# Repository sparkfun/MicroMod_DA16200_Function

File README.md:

SparkFun MicroMod DA16200 Function Board
========================================

[*SparkFun MicroMod DA16200 Function Board (18594)*](https://www.sparkfun.com/products/18594)

The SparkFun MicroMod DA16200 Function Board adds a fully integrated WiFi module with a 40MHz crystal oscillator, 32.768KHz RTC clock, RF Lumped RF filter, 4MB flash memory, and an on-board chip antenna to any MicroMod project. With the addition of JTAG connectors for deep dive programming, you've got everything you need to get your MicroMod setup ready for your next IoT project. 

The SparkFun MicroMod DA16200 Function Board is ideal for MicroMod projects involving door locks, thermostats, sensors, pet trackers, and other home IoT projects, thanks in part to the multiple sleep modes that allow you to take advantage of current draws as low as 0.2uA-3.5uA.

Additionally, the DA16200 module's certified WiFi alliance for IEEE802.11b/g/n, WiFi Direct, and WPS functionalities means that it has been approved for use by multiple countries and using the WiFi Alliance transfer policy, each WiFi Certification can be transferred without being tested again. 

Repository Contents
-------------------
* **/Hardware** - Eagle design files (.brd, .sch)

Documentation
--------------
* **[Hookup Guide](https://learn.sparkfun.com/tutorials/micromod-wifi-function-board---da16200-hookup-guide)** - Basic hookup guide for the SparkFun MicroMod DA16200 Function Board.

License Information
-------------------

This product is _**open source**_! 

Please review the LICENSE.md file for license information. 

If you have any questions or concerns on licensing, please contact technical support on our [SparkFun forums](https://forum.sparkfun.com/viewforum.php?f=152).

Distributed as-is; no warranty is given.

- Your friends at SparkFun.

_<COLLABORATION CREDIT>_

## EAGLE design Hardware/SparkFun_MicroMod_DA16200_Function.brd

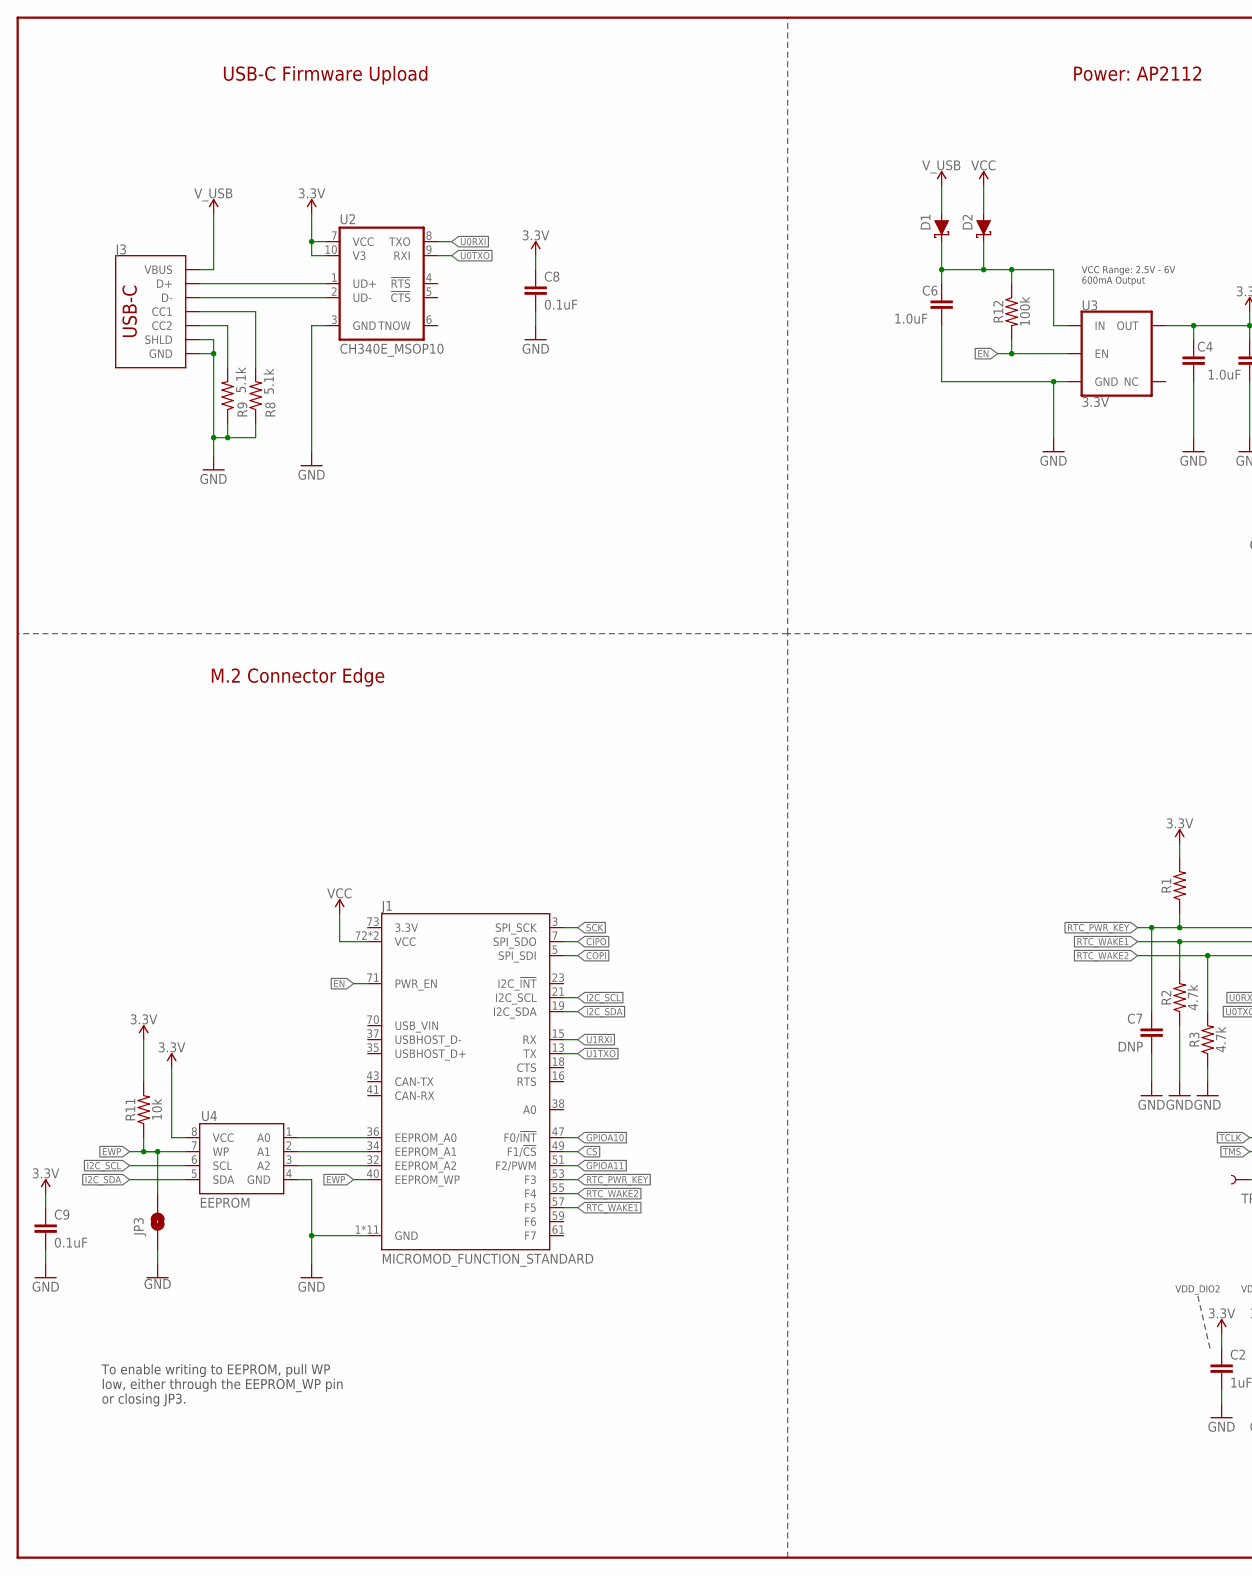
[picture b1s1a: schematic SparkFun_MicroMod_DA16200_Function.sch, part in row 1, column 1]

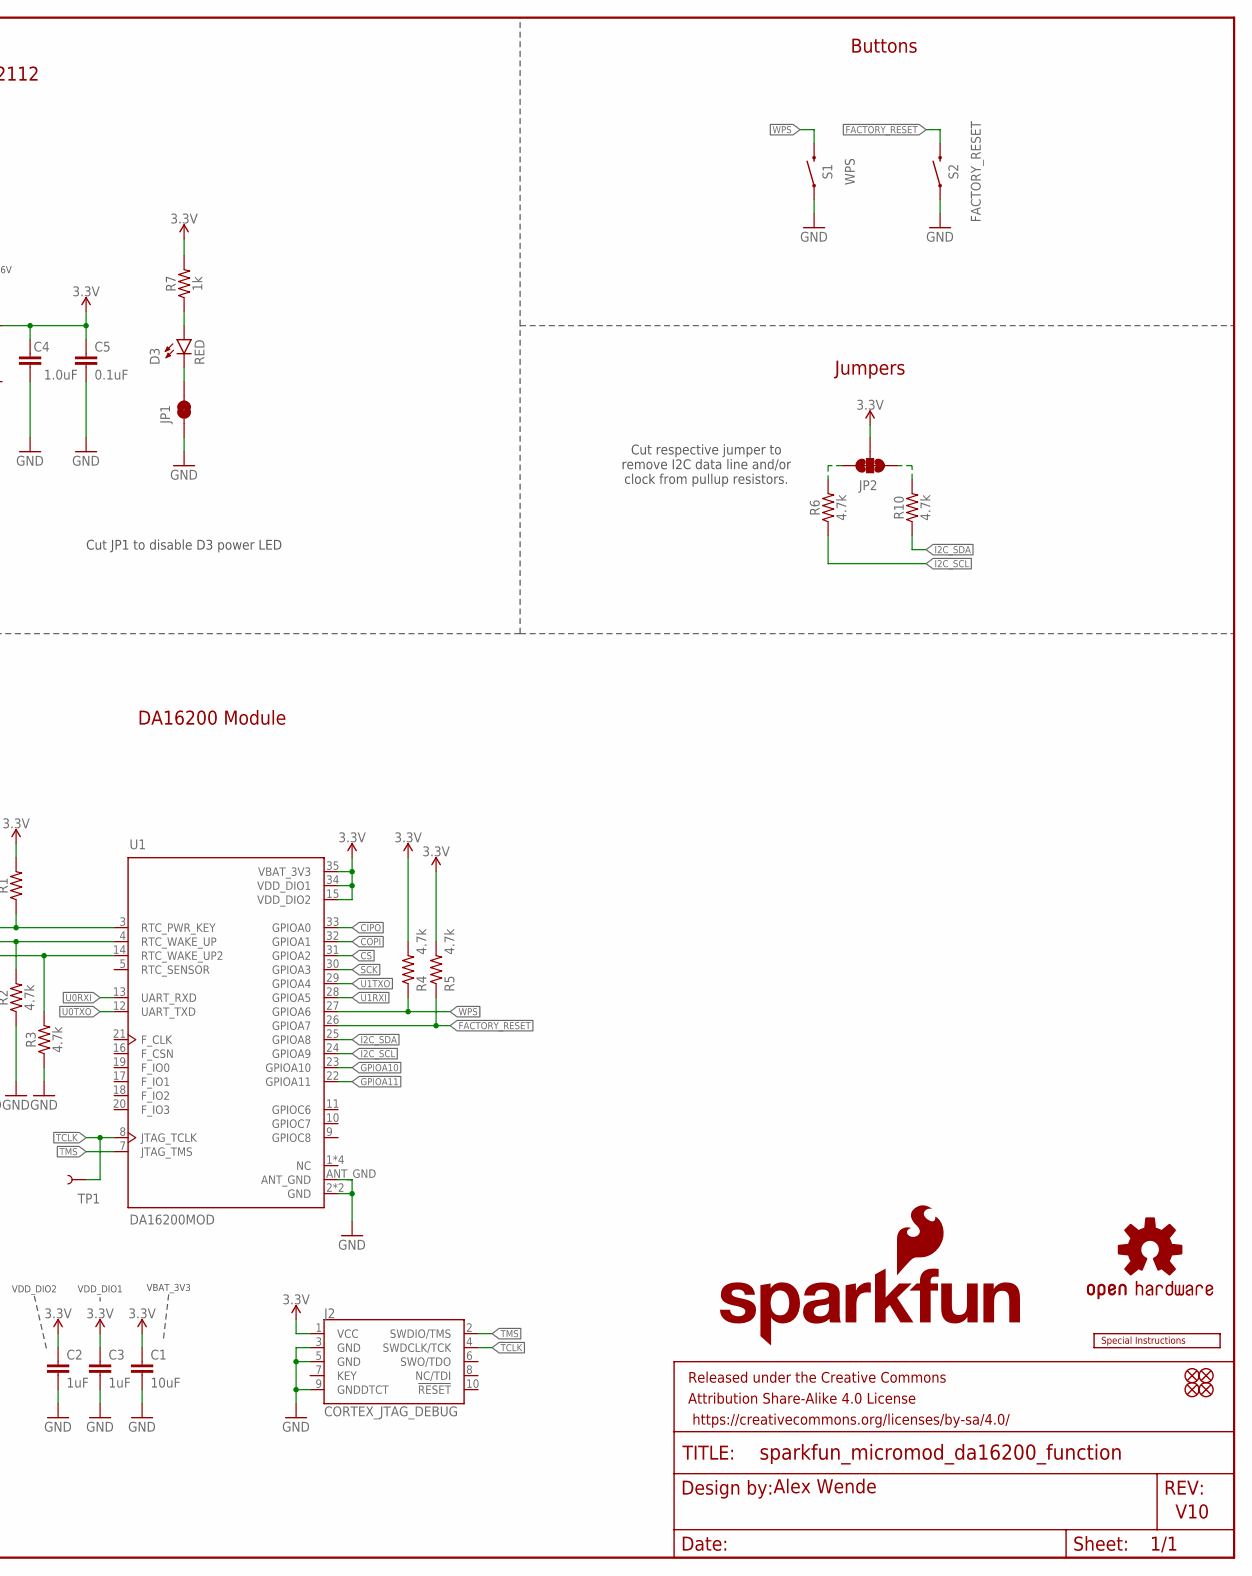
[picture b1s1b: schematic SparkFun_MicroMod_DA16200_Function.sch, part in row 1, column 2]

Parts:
C1: 10uF; 0603
C2, C3: 1uF; 0603
C4, C6: 1.0uF; 0603
C5, C8, C9: 0.1uF; 0603
C7: DNP; 0603
D1, D2: DIODE-SCHOTTKY-BAT60A; SOD-323
D3: RED; LED-0603
FD1, FD2, FD3, FD4: FIDUCIAL1X2; FIDUCIAL-1X2
FRAME2: FRAME-LEDGER; CREATIVE_COMMONS
J1: MICROMOD_FUNCTION_STANDARD; M.2-CARD-E-22_FUNCTION_STANDARD
J2: CORTEX_JTAG_DEBUG; 2X5-PTH-1.27MM-NO_SILK
J3: USB_C_2-LAYER_PADS; USB-C-16P-2LAYER-PADS
JP1: JUMPER-SMT_2_NC_TRACE_SILK; SMT-JUMPER_2_NC_TRACE_SILK
JP2: JUMPER-SMT_3_2-NC_TRACE_SILK; SMT-JUMPER_3_2-NC_TRACE_SILK
JP3: JUMPER-SMT_2_NO_SILK; SMT-JUMPER_2_NO_SILK
LOGO1: SFE_LOGO_NAME_FLAME.2_INCH; SFE_LOGO_NAME_FLAME_.2
LOGO2: OSHW-LOGOS; OSHW-LOGO-S
LOGO3: SPECIAL_INSTRUCTIONS-ORDERING; ORDERING_INSTRUCTIONS
R1: 0603
R2, R3, R4, R5, R6, R10: 4.7k; 0603
R7: 1k; 0402-TIGHT
R8, R9: 5.1k; 0402-TIGHT
R11: 10k; 0603
R12: 100k; 0603
S1: WPS; TACTILE_SWITCH_SMD_5.2MM
S2: FACTORY_RESET; TACTILE_SWITCH_SMD_5.2MM
TP1: TEST-POINT3; PAD.03X.03
U1: DA16200MOD; XCVR_DA16200MOD-AAC4WA32
U2: CH340E_MSOP10; MSOP10
U3: 3.3V; SOT23-5
U4: EEPROM; SO08

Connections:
3.3V: C1.1, C2.1, C3.1, C4.1, C5.1, C8.1, C9.1, J2.1 (VCC), JP2.2, R1.2, R4.2, R5.2, R7.2, R11.2, U1.15 (VDD_DIO2), U1.34 (VDD_DIO1), U1.35 (VBAT_3V3), U2.7 (VCC), U2.10 (V3), U3.5 (OUT), U4.8 (VCC)
!CS!: J1.49 (F1/!CS!), U1.31 (GPIOA2)
CIPO: J1.7 (SPI_SDO), U1.33 (GPIOA0)
COPI: J1.5 (SPI_SDI), U1.32 (GPIOA1)
EN: J1.71 (PWR_EN), R12.2, U3.3 (EN)
EWP: J1.40 (EEPROM_WP), JP3.2, R11.1, U4.7 (WP)
FACTORY_RESET: R5.1, S2.3 (2), U1.26 (GPIOA7)
GND: C1.2, C2.2, C3.2, C4.2, C5.2, C6.2, C7.2, C8.2, C9.2, J1.1 (GND), J1.33 (GND), J1.39 (GND), J1.45 (GND), J1.75 (GND), J1.GND1 (GND), J1.GND2 (GND), J1.GND3 (GND), J1.GND4 (GND), J1.GND5 (GND), J1.GND6 (GND), J2.3 (GND), J2.5 (GND), J2.9 (GNDDTCT), J3.GND, J3.GND2 (GND), J3.SHLD1 (SHLD), J3.SHLD2 (SHLD), J3.SHLD3 (SHLD), J3.SHLD4 (SHLD), JP1.1, JP3.1, R2.1, R3.1, R8.1, R9.1, S1.1, S2.1, U1.2 (GND), U1.ANT_GND, U1.GND, U2.3 (GND), U3.2 (GND), U4.4 (GND)
GPIOA10: J1.47 (F0/!INT!), U1.23 (GPIOA10)
GPIOA11: J1.51 (F2/PWM), U1.22 (GPIOA11)
I2C_SCL: J1.21 (I2C_SCL), R6.1, U1.24 (GPIOA9), U4.6 (SCL)
I2C_SDA: J1.19 (I2C_SDA), R10.1, U1.25 (GPIOA8), U4.5 (SDA)
unnamed: J1.36 (EEPROM_A0), U4.1 (A0)
unnamed: J3.A5 (CC1), R8.2
unnamed: C6.1, D1.C, D2.C, R12.1, U3.1 (IN)
unnamed: J3.B5 (CC2), R9.2
unnamed: D3.C, JP1.2
unnamed: D3.A, R7.1
unnamed: J1.32 (EEPROM_A2), U4.3 (A2)
unnamed: J1.34 (EEPROM_A1), U4.2 (A1)
unnamed: J3.A6 (D+), J3.B6 (D+), U2.1 (UD+)
unnamed: J3.A7 (D-), J3.B7 (D-), U2.2 (UD-)
unnamed: JP2.1, R10.2
unnamed: JP2.3, R6.2
RTC_PWR_KEY: C7.1, J1.53 (F3), R1.1, U1.3 (RTC_PWR_KEY)
RTC_WAKE1: J1.57 (F5), R2.2, U1.4 (RTC_WAKE_UP)
RTC_WAKE2: J1.55 (F4), R3.2, U1.14 (RTC_WAKE_UP2)
SCK: J1.3 (SPI_SCK), U1.30 (GPIOA3)
TCLK: J2.4 (SWDCLK/TCK), TP1.1, U1.8 (JTAG_TCLK)
TMS: J2.2 (SWDIO/TMS), U1.7 (JTAG_TMS)
U0RXI: U1.13 (UART_RXD), U2.8 (TXO)
U0TXO: U1.12 (UART_TXD), U2.9 (RXI)
U1RXI: J1.15 (RX), U1.28 (GPIOA5)
U1TXO: J1.13 (TX), U1.29 (GPIOA4)
VCC: D2.A, J1.72 (VCC), J1.74 (VCC)
V_USB: D1.A, J3.VBUS1 (VBUS), J3.VBUS2 (VBUS)
WPS: R4.1, S1.3 (2), U1.27 (GPIOA6)

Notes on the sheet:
VCC Range: 2.5V - 6V 600mA Output
VDD_DIO2
VDD_DIO1
VBAT_3V3
Alex Wende
V10
USB-C Firmware Upload
DA16200 Module
M.2 Connector Edge
Power: AP2112
Buttons
Jumpers
Cut respective jumper to remove I2C data line and/or clock from pullup resistors.
To enable writing to EEPROM, pull WP low, either through the EEPROM_WP pin or closing JP3.
Cut JP1 to disable D3 power LED

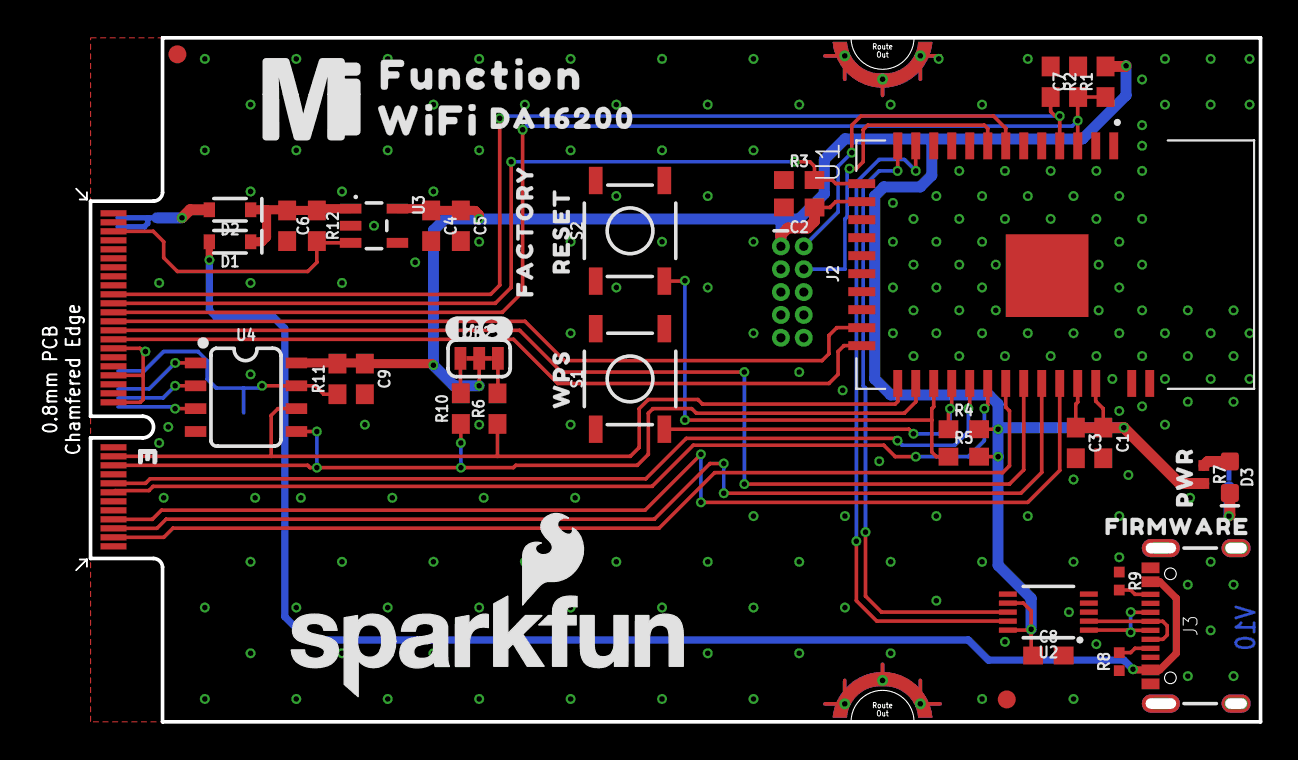
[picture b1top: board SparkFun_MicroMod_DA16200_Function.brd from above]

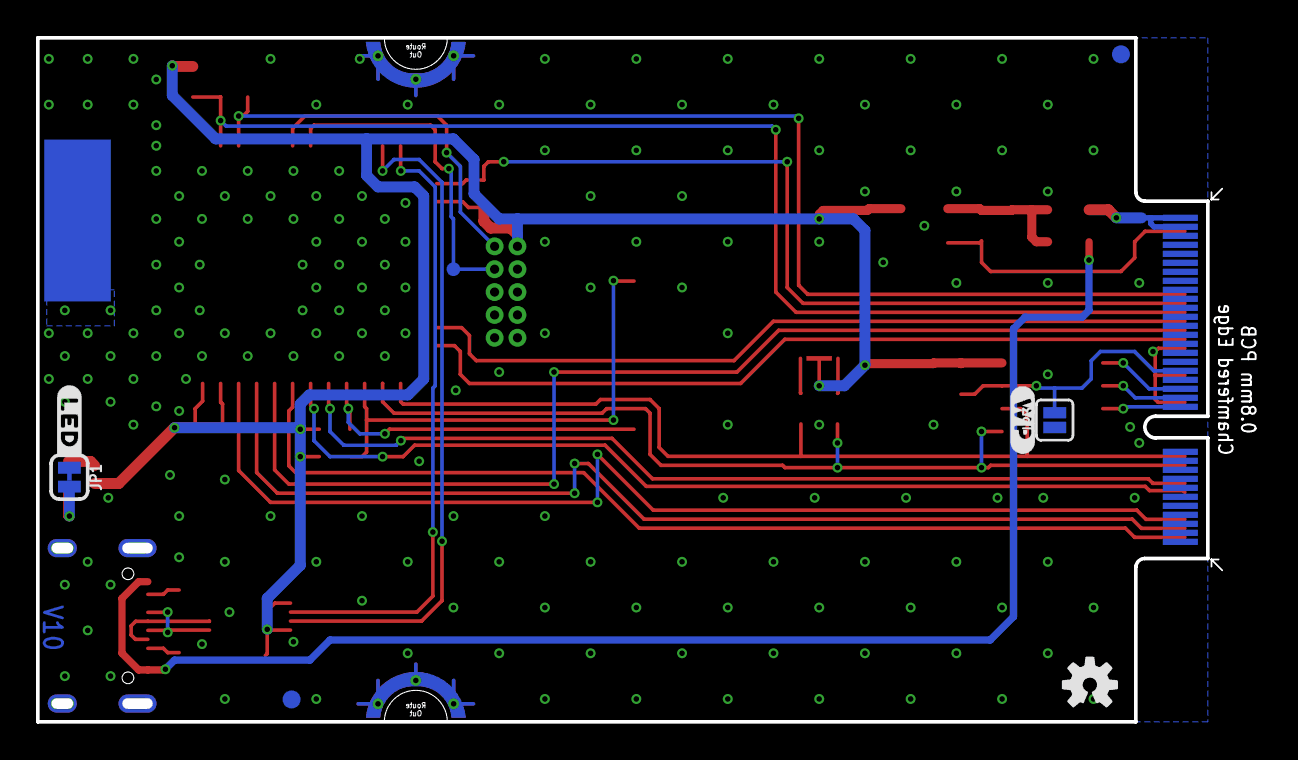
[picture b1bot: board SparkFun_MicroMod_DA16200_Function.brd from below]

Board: 2 copper layers, 65.8 x 38.0 mm, 57 parts (8 on the bottom side), 37 nets.

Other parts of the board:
U$1: FIRMWARE0
U$2: PWR0
U$3: #LED#0
U$4: FUNCTION0
U$5: DA162000
U$6: WIFI0
U$7: WPS0
U$8: FACTORY0
U$9: RESET0
U$10: #WP#0
U$11: #I2C#0
U$12: MICROMOD_MI_LOGO_1

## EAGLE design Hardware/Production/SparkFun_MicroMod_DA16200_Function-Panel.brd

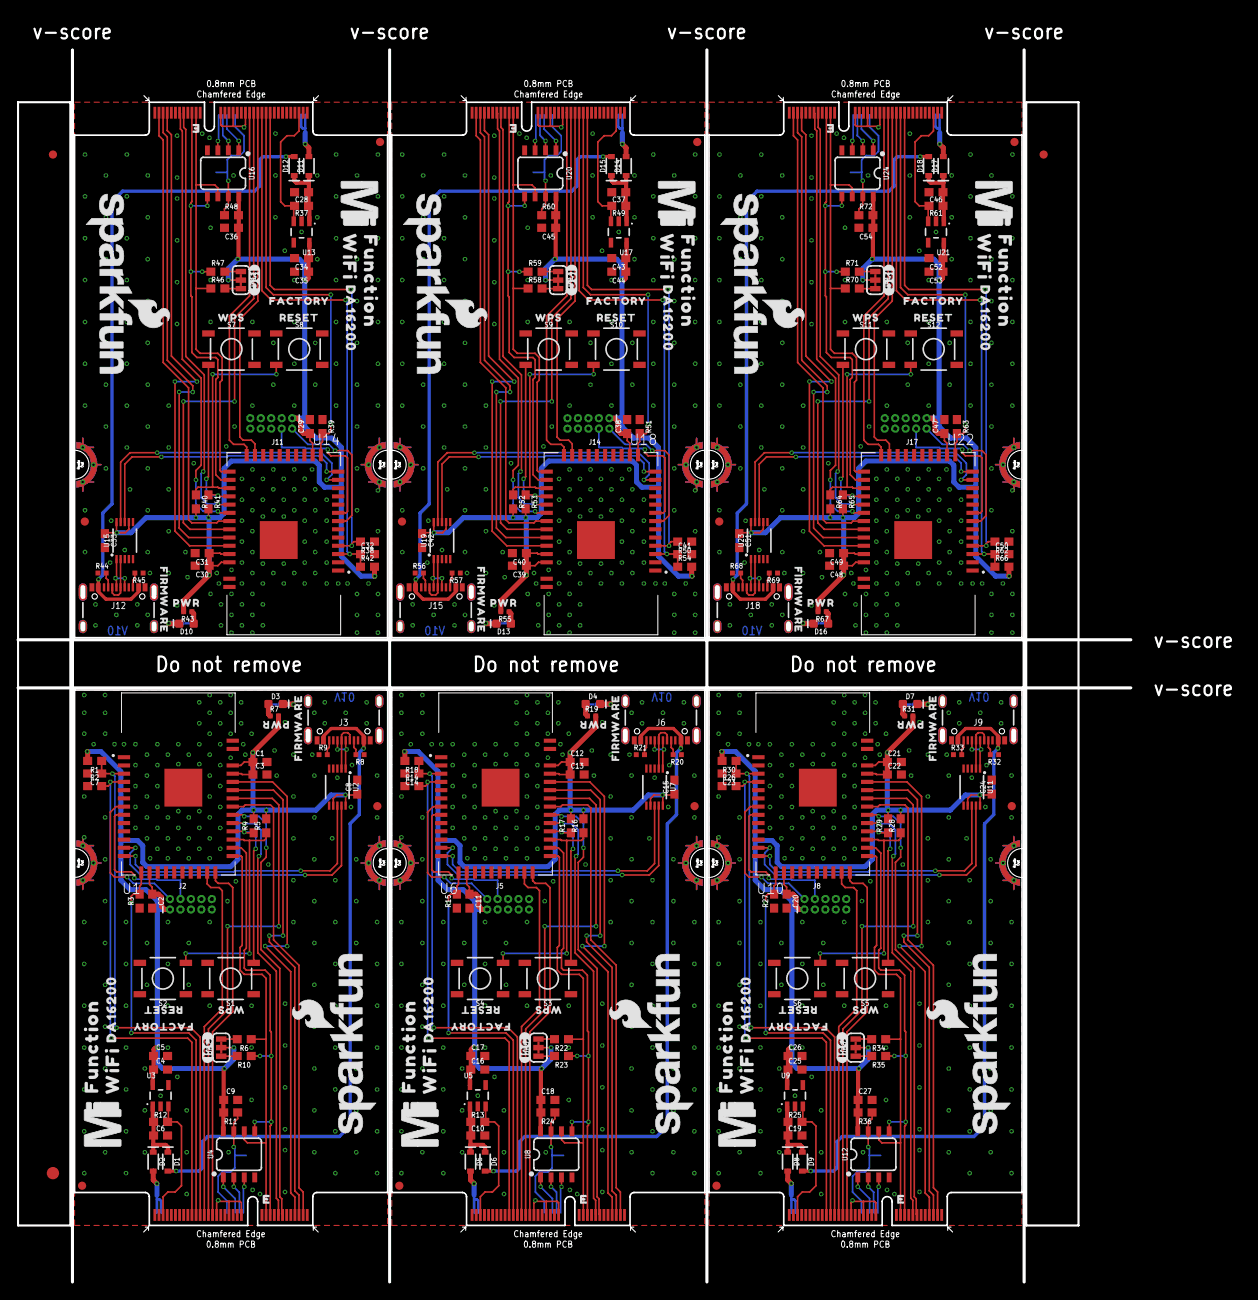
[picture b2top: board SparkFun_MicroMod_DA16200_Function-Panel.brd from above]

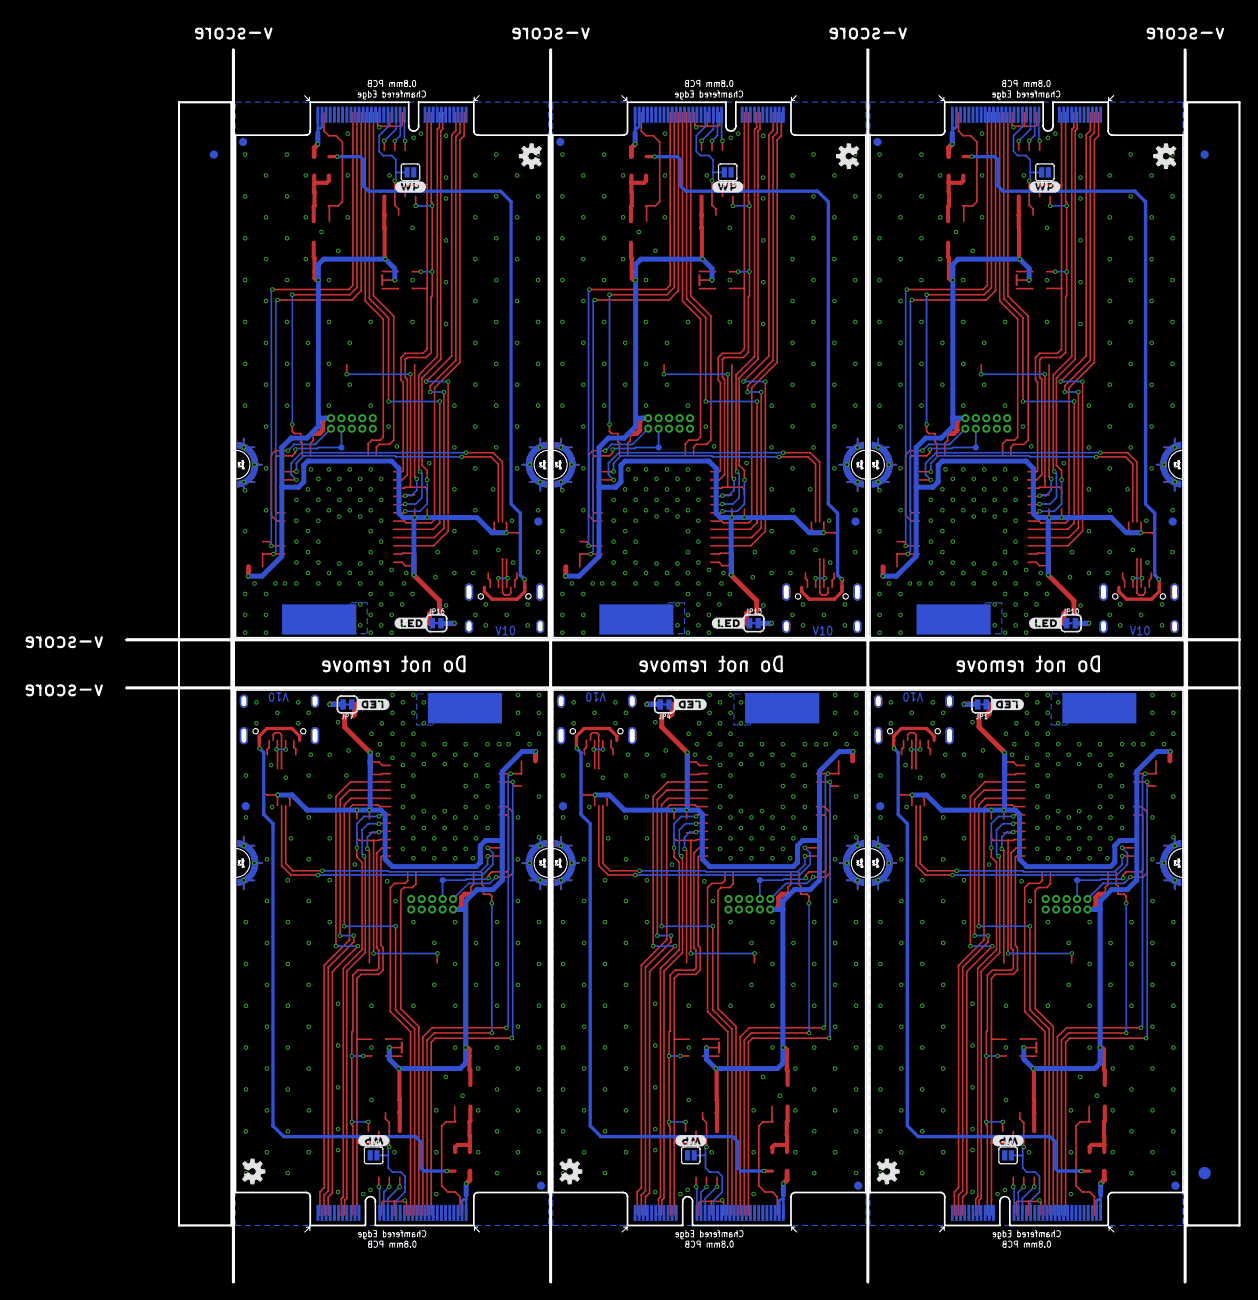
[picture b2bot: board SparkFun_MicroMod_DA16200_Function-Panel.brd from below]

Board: 2 copper layers, 135.1 x 149.6 mm, 336 parts (51 on the bottom side), 222 nets.

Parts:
C1, C12, C21, C30, C39, C48: 10uF; 0603
C2, C3, C11, C13, C20, C22, C29, C31, C38, C40, C47, C49: 1uF; 0603
C4, C6, C10, C16, C19, C25, C28, C34, C37, C43, C46, C52: 1.0uF; 0603
C5, C8, C9, C15, C17, C18, C24, C26, C27, C33, C35, C36, C42, C44, C45, C51, C53, C54: 0.1uF; 0603
C7, C14, C23, C32, C41, C50: DNP; 0603
D1, D2, D5, D6, D8, D9, D11, D12, D14, D15, D17, D18: SOD-323
D3, D4, D7, D10, D13, D16: RED; LED-0603
E$1, E$2, E$3, E$4: FIDUCIAL-1X2
E$5, E$6: FIDUCIAL-1.5X3
FD1, FD2, FD3, FD4, FD5, FD6, FD7, FD8, FD9, FD10, FD11, FD12, FD13, FD14, FD15, FD16, FD17, FD18, FD19, FD20, FD21, FD22, FD23, FD24: FIDUCIAL1X2; FIDUCIAL-1X2
J1, J4, J7, J10, J13, J16: MICROMOD_STANDARD; M.2-CARD-E-22_FUNCTION_STANDARD
J2, J5, J8, J11, J14, J17: CORTEX_JTAG_DEBUG; 2X5-PTH-1.27MM-NO_SILK
J3, J6, J9, J12, J15, J18: USB-C-16P-2LAYER-PADS
JP1, JP4, JP7, JP10, JP13, JP16: JUMPER-SMT_2_NC_TRACE_SILK; SMT-JUMPER_2_NC_TRACE_SILK
JP2, JP5, JP8, JP11, JP14, JP17: JUMPER-SMT_3_2-NC_TRACE_SILK; SMT-JUMPER_3_2-NC_TRACE_SILK
JP3, JP6, JP9, JP12, JP15, JP18: SMT-JUMPER_2_NO_SILK
LOGO1, LOGO3, LOGO5, LOGO7, LOGO9, LOGO11: SFE_LOGO_NAME_FLAME.2_INCH; SFE_LOGO_NAME_FLAME_.2
LOGO2, LOGO4, LOGO6, LOGO8, LOGO10, LOGO12: OSHW-LOGOS; OSHW-LOGO-S
R1, R18, R30, R42, R54, R66: DNP; 0603
R2, R3, R4, R5, R6, R10, R14, R15, R16, R17, R22, R23, R26, R27, R28, R29, R34, R35, R38, R39, R40, R41, R46, R47, R50, R51, R52, R53, R58, R59, R62, R63, R64, R65, R70, R71: 4.7k; 0603
R7, R19, R31, R43, R55, R67: 1k; 0402-TIGHT
R8, R9, R20, R21, R32, R33, R44, R45, R56, R57, R68, R69: 5.1k; 0402-TIGHT
R11, R24, R36, R48, R60, R72: 10k; 0603
R12, R13, R25, R37, R49, R61: 100k; 0603
S1, S3, S5, S7, S9, S11: WPS; TACTILE_SWITCH_SMD_5.2MM
S2, S4, S6, S8, S10, S12: FACTORY_RESET; TACTILE_SWITCH_SMD_5.2MM
TP1, TP2, TP3, TP4, TP5, TP6: PAD.03X.03
U1, U6, U10, U14, U18, U22: DA16200MOD; XCVR_DA16200MOD-AAC4WA32
U2, U7, U11, U15, U19, U23: CH340E_MSOP10; MSOP10
U3, U5, U9, U13, U17, U21: 3.3V; SOT23-5
U4, U8, U12, U16, U20, U24: EEPROM; SO08
U$1, U$13, U$25, U$37, U$49, U$61: FIRMWARE0
U$2, U$14, U$26, U$38, U$50, U$62: PWR0
U$3, U$15, U$27, U$39, U$51, U$63: #LED#0
U$4, U$16, U$28, U$40, U$52, U$64: FUNCTION0
U$5, U$17, U$29, U$41, U$53, U$65: DA162000
U$6, U$23, U$35, U$47, U$59, U$71: WIFI0
U$7, U$18, U$30, U$42, U$54, U$66: WPS0
U$8, U$19, U$31, U$43, U$55, U$67: FACTORY0
U$9, U$20, U$32, U$44, U$56, U$68: RESET0
U$10, U$24, U$36, U$48, U$60, U$72: #WP#0
U$11, U$21, U$33, U$45, U$57, U$69: #I2C#0
U$12, U$22, U$34, U$46, U$58, U$70: MICROMOD_MI_LOGO_1

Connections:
3.3V: C1.1, C2.1, C3.1, C4.1, C5.1, C8.1, C9.1, J2.1, JP2.2, R1.2, R4.2, R5.2, R7.2, R11.2, U1.15, U1.34, U1.35, U2.7, U2.10, U3.5, U4.8
3.3V1: C11.1, C12.1, C13.1, C15.1, C16.1, C17.1, C18.1, J5.1, JP5.2, R16.2, R17.2, R18.2, R19.2, R24.2, U5.5, U6.15, U6.34, U6.35, U7.7, U7.10, U8.8
3.3V2: C20.1, C21.1, C22.1, C24.1, C25.1, C26.1, C27.1, J8.1, JP8.2, R28.2, R29.2, R30.2, R31.2, R36.2, U9.5, U10.15, U10.34, U10.35, U11.7, U11.10, U12.8
3.3V3: C29.1, C30.1, C31.1, C33.1, C34.1, C35.1, C36.1, J11.1, JP11.2, R40.2, R41.2, R42.2, R43.2, R48.2, U13.5, U14.15, U14.34, U14.35, U15.7, U15.10, U16.8
3.3V4: C38.1, C39.1, C40.1, C42.1, C43.1, C44.1, C45.1, J14.1, JP14.2, R52.2, R53.2, R54.2, R55.2, R60.2, U17.5, U18.15, U18.34, U18.35, U19.7, U19.10, U20.8
3.3V5: C47.1, C48.1, C49.1, C51.1, C52.1, C53.1, C54.1, J17.1, JP17.2, R64.2, R65.2, R66.2, R67.2, R72.2, U21.5, U22.15, U22.34, U22.35, U23.7, U23.10, U24.8
!CS!: J1.49, U1.31
!CS!1: J4.49, U6.31
!CS!2: J7.49, U10.31
!CS!3: J10.49, U14.31
!CS!4: J13.49, U18.31
!CS!5: J16.49, U22.31
CIPO: J1.7, U1.33
CIPO1: J4.7, U6.33
CIPO2: J7.7, U10.33
CIPO3: J10.7, U14.33
CIPO4: J13.7, U18.33
CIPO5: J16.7, U22.33
COPI: J1.5, U1.32
COPI1: J4.5, U6.32
COPI2: J7.5, U10.32
COPI3: J10.5, U14.32
COPI4: J13.5, U18.32
COPI5: J16.5, U22.32
EN: J1.71, R12.2, U3.3
EN1: J4.71, R13.2, U5.3
EN2: J7.71, R25.2, U9.3
EN3: J10.71, R37.2, U13.3
EN4: J13.71, R49.2, U17.3
EN5: J16.71, R61.2, U21.3
EWP: J1.40, JP3.2, R11.1, U4.7
EWP1: J4.40, JP6.2, R24.1, U8.7
EWP2: J7.40, JP9.2, R36.1, U12.7
EWP3: J10.40, JP12.2, R48.1, U16.7
EWP4: J13.40, JP15.2, R60.1, U20.7
EWP5: J16.40, JP18.2, R72.1, U24.7
FACTORY_RESET: R5.1, S2.3, U1.26
FACTORY_RESET1: R16.1, S4.3, U6.26
FACTORY_RESET2: R28.1, S6.3, U10.26
FACTORY_RESET3: R40.1, S8.3, U14.26
FACTORY_RESET4: R52.1, S10.3, U18.26
FACTORY_RESET5: R64.1, S12.3, U22.26
GND: C1.2, C2.2, C3.2, C4.2, C5.2, C6.2, C7.2, C8.2, C9.2, J1.1, J1.33, J1.39, J1.45, J1.75, J1.GND1, J1.GND2, J1.GND3, J1.GND4, J1.GND5, J1.GND6, J2.3, J2.5, J2.9, J3.GND, J3.GND2, J3.SHLD1, J3.SHLD2, J3.SHLD3, J3.SHLD4, JP1.1, JP3.1, R2.1, R3.1, R8.1, R9.1, S1.1, S2.1, U1.2, U1.ANT_GND, U1.GND, U2.3, U3.2, U4.4
GND1: C10.2, C11.2, C12.2, C13.2, C14.2, C15.2, C16.2, C17.2, C18.2, J4.1, J4.33, J4.39, J4.45, J4.75, J4.GND1, J4.GND2, J4.GND3, J4.GND4, J4.GND5, J4.GND6, J5.3, J5.5, J5.9, J6.GND, J6.GND2, J6.SHLD1, J6.SHLD2, J6.SHLD3, J6.SHLD4, JP4.1, JP6.1, R14.1, R15.1, R20.1, R21.1, S3.1, S4.1, U5.2, U6.2, U6.ANT_GND, U6.GND, U7.3, U8.4
GND2: C19.2, C20.2, C21.2, C22.2, C23.2, C24.2, C25.2, C26.2, C27.2, J7.1, J7.33, J7.39, J7.45, J7.75, J7.GND1, J7.GND2, J7.GND3, J7.GND4, J7.GND5, J7.GND6, J8.3, J8.5, J8.9, J9.GND, J9.GND2, J9.SHLD1, J9.SHLD2, J9.SHLD3, J9.SHLD4, JP7.1, JP9.1, R26.1, R27.1, R32.1, R33.1, S5.1, S6.1, U9.2, U10.2, U10.ANT_GND, U10.GND, U11.3, U12.4
GND3: C28.2, C29.2, C30.2, C31.2, C32.2, C33.2, C34.2, C35.2, C36.2, J10.1, J10.33, J10.39, J10.45, J10.75, J10.GND1, J10.GND2, J10.GND3, J10.GND4, J10.GND5, J10.GND6, J11.3, J11.5, J11.9, J12.GND, J12.GND2, J12.SHLD1, J12.SHLD2, J12.SHLD3, J12.SHLD4, JP10.1, JP12.1, R38.1, R39.1, R44.1, R45.1, S7.1, S8.1, U13.2, U14.2, U14.ANT_GND, U14.GND, U15.3, U16.4
GND4: C37.2, C38.2, C39.2, C40.2, C41.2, C42.2, C43.2, C44.2, C45.2, J13.1, J13.33, J13.39, J13.45, J13.75, J13.GND1, J13.GND2, J13.GND3, J13.GND4, J13.GND5, J13.GND6, J14.3, J14.5, J14.9, J15.GND, J15.GND2, J15.SHLD1, J15.SHLD2, J15.SHLD3, J15.SHLD4, JP13.1, JP15.1, R50.1, R51.1, R56.1, R57.1, S9.1, S10.1, U17.2, U18.2, U18.ANT_GND, U18.GND, U19.3, U20.4
GND5: C46.2, C47.2, C48.2, C49.2, C50.2, C51.2, C52.2, C53.2, C54.2, J16.1, J16.33, J16.39, J16.45, J16.75, J16.GND1, J16.GND2, J16.GND3, J16.GND4, J16.GND5, J16.GND6, J17.3, J17.5, J17.9, J18.GND, J18.GND2, J18.SHLD1, J18.SHLD2, J18.SHLD3, J18.SHLD4, JP16.1, JP18.1, R62.1, R63.1, R68.1, R69.1, S11.1, S12.1, U21.2, U22.2, U22.ANT_GND, U22.GND, U23.3, U24.4
GPIOA1: J4.47, U6.23
GPIOA2: J4.51, U6.22
GPIOA3: J7.47, U10.23
GPIOA4: J7.51, U10.22
GPIOA5: J10.47, U14.23
GPIOA6: J10.51, U14.22
GPIOA7: J13.47, U18.23
GPIOA8: J13.51, U18.22
GPIOA9: J16.47, U22.23
GPIOA10: J1.47, U1.23
GPIOA11: J1.51, U1.22
GPIOA12: J16.51, U22.22
I2C_SCL: J1.21, R6.1, U1.24, U4.6
I2C_SCL1: J4.21, R22.1, U6.24, U8.6
I2C_SCL2: J7.21, R34.1, U10.24, U12.6
I2C_SCL3: J10.21, R46.1, U14.24, U16.6
I2C_SCL4: J13.21, R58.1, U18.24, U20.6
I2C_SCL5: J16.21, R70.1, U22.24, U24.6
I2C_SDA: J1.19, R10.1, U1.25, U4.5
I2C_SDA1: J4.19, R23.1, U6.25, U8.5
I2C_SDA2: J7.19, R35.1, U10.25, U12.5
I2C_SDA3: J10.19, R47.1, U14.25, U16.5
I2C_SDA4: J13.19, R59.1, U18.25, U20.5
I2C_SDA5: J16.19, R71.1, U22.25, U24.5
unnamed: J1.36, U4.1
unnamed: J3.A5, R8.2
unnamed: C6.1, D1.C, D2.C, R12.1, U3.1
unnamed: D4.C, JP4.2
unnamed: J3.B5, R9.2
unnamed: D3.C, JP1.2
unnamed: D3.A, R7.1
unnamed: J1.32, U4.3
unnamed: J1.34, U4.2
unnamed: J3.A6, J3.B6, U2.1
unnamed: J3.A7, J3.B7, U2.2
unnamed: D4.A, R19.1
unnamed: JP2.1, R10.2
unnamed: JP2.3, R6.2
unnamed: J6.A5, R20.2
unnamed: J6.B5, R21.2
unnamed: J6.A6, J6.B6, U7.1
unnamed: J6.A7, J6.B7, U7.2
unnamed: J4.32, U8.3
unnamed: J4.34, U8.2
unnamed: J4.36, U8.1
unnamed: JP5.1, R23.2
unnamed: JP5.3, R22.2
unnamed: C10.1, D5.C, D6.C, R13.1, U5.1
unnamed: D7.C, JP7.2
unnamed: D7.A, R31.1
unnamed: J9.A5, R32.2
unnamed: J9.B5, R33.2
unnamed: J9.A6, J9.B6, U11.1
unnamed: J9.A7, J9.B7, U11.2
unnamed: J7.32, U12.3
unnamed: J7.34, U12.2
unnamed: J7.36, U12.1
unnamed: JP8.1, R35.2
unnamed: JP8.3, R34.2
unnamed: C19.1, D8.C, D9.C, R25.1, U9.1
unnamed: D10.C, JP10.2
unnamed: D10.A, R43.1
unnamed: J12.A5, R44.2
unnamed: J12.B5, R45.2
unnamed: J12.A6, J12.B6, U15.1
unnamed: J12.A7, J12.B7, U15.2
unnamed: J10.32, U16.3
unnamed: J10.34, U16.2
unnamed: J10.36, U16.1
unnamed: JP11.1, R47.2
unnamed: JP11.3, R46.2
unnamed: C28.1, D11.C, D12.C, R37.1, U13.1
unnamed: D13.C, JP13.2
unnamed: D13.A, R55.1
unnamed: J15.A5, R56.2
unnamed: J15.B5, R57.2
unnamed: J15.A6, J15.B6, U19.1
unnamed: J15.A7, J15.B7, U19.2
unnamed: J13.32, U20.3
unnamed: J13.34, U20.2
unnamed: J13.36, U20.1
unnamed: JP14.1, R59.2
unnamed: JP14.3, R58.2
unnamed: C37.1, D14.C, D15.C, R49.1, U17.1
unnamed: D16.C, JP16.2
unnamed: D16.A, R67.1
unnamed: J18.A5, R68.2
unnamed: J18.B5, R69.2
unnamed: J18.A6, J18.B6, U23.1
unnamed: J18.A7, J18.B7, U23.2
unnamed: J16.32, U24.3
unnamed: J16.34, U24.2
unnamed: J16.36, U24.1
unnamed: JP17.1, R71.2
unnamed: JP17.3, R70.2
unnamed: C46.1, D17.C, D18.C, R61.1, U21.1
RTC_PWR_KEY: C7.1, J1.53, R1.1, U1.3
RTC_PWR_KEY1: C14.1, J4.53, R18.1, U6.3
RTC_PWR_KEY2: C23.1, J7.53, R30.1, U10.3
RTC_PWR_KEY3: C32.1, J10.53, R42.1, U14.3
RTC_PWR_KEY4: C41.1, J13.53, R54.1, U18.3
RTC_PWR_KEY5: C50.1, J16.53, R66.1, U22.3
RTC_WAKE1: J1.57, R2.2, U1.4
RTC_WAKE2: J1.55, R3.2, U1.14
RTC_WAKE3: J4.57, R14.2, U6.4
RTC_WAKE4: J4.55, R15.2, U6.14
RTC_WAKE5: J7.57, R26.2, U10.4
RTC_WAKE6: J7.55, R27.2, U10.14
RTC_WAKE7: J10.57, R38.2, U14.4
RTC_WAKE8: J10.55, R39.2, U14.14
RTC_WAKE9: J13.57, R50.2, U18.4
RTC_WAKE10: J13.55, R51.2, U18.14
RTC_WAKE11: J16.57, R62.2, U22.4
RTC_WAKE12: J16.55, R63.2, U22.14
SCK: J1.3, U1.30
SCK1: J4.3, U6.30
SCK2: J7.3, U10.30
SCK3: J10.3, U14.30
SCK4: J13.3, U18.30
SCK5: J16.3, U22.30
TCLK: J2.4, TP1.1, U1.8
TCLK1: J5.4, TP2.1, U6.8
TCLK2: J8.4, TP3.1, U10.8
TCLK3: J11.4, TP4.1, U14.8
TCLK4: J14.4, TP5.1, U18.8
TCLK5: J17.4, TP6.1, U22.8
TMS: J2.2, U1.7
TMS1: J5.2, U6.7
TMS2: J8.2, U10.7
TMS3: J11.2, U14.7
TMS4: J14.2, U18.7
TMS5: J17.2, U22.7
U0RXI: U1.13, U2.8
U0RXI1: U6.13, U7.8
U0RXI2: U10.13, U11.8
U0RXI3: U14.13, U15.8
U0RXI4: U18.13, U19.8
U0RXI5: U22.13, U23.8
U0TXO: U1.12, U2.9
U0TXO1: U6.12, U7.9
U0TXO2: U10.12, U11.9
U0TXO3: U14.12, U15.9
U0TXO4: U18.12, U19.9
U0TXO5: U22.12, U23.9
U1RXI: J1.15, U1.28
U1RXI1: J4.15, U6.28
U1RXI2: J7.15, U10.28
U1RXI3: J10.15, U14.28
U1RXI4: J13.15, U18.28
U1RXI5: J16.15, U22.28
U1TXO: J1.13, U1.29
U1TXO1: J4.13, U6.29
U1TXO2: J7.13, U10.29
U1TXO3: J10.13, U14.29
U1TXO4: J13.13, U18.29
U1TXO5: J16.13, U22.29
VCC: D2.A, J1.72, J1.74
VCC1: D5.A, J4.72, J4.74
VCC2: D8.A, J7.72, J7.74
VCC3: D11.A, J10.72, J10.74
VCC4: D14.A, J13.72, J13.74
VCC5: D17.A, J16.72, J16.74
V_USB: D1.A, J3.VBUS1, J3.VBUS2
V_USB1: D6.A, J6.VBUS1, J6.VBUS2
V_USB2: D9.A, J9.VBUS1, J9.VBUS2
V_USB3: D12.A, J12.VBUS1, J12.VBUS2
V_USB4: D15.A, J15.VBUS1, J15.VBUS2
V_USB5: D18.A, J18.VBUS1, J18.VBUS2
WPS: R4.1, S1.3, U1.27
WPS1: R17.1, S3.3, U6.27
WPS2: R29.1, S5.3, U10.27
WPS3: R41.1, S7.3, U14.27
WPS4: R53.1, S9.3, U18.27
WPS5: R65.1, S11.3, U22.27

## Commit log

2021-08-20 Update SparkFun_MicroMod_DA16200_Function.sch
    Added labels
2021-08-20 Update SparkFun_MicroMod_DA16200_Function.brd
    Added designer and measures
2021-08-23 Design Review Changes
    Swapped U1RX/TX
    Corrected SCL/SDA
    Added a few more vias on the PCB
2021-08-23 Added Ordering Instructions
2021-09-17 V10
    Added EEPROM, I2C Pullups
2021-09-21 V10 update
    Added diodes for VIN and VUSB
2021-09-24 V10 EEPROM changes
    Added pullup, jumper, and MM pin map for EEPROM WP pin
2021-09-28 Added panel
2021-10-27 Create README.md
    First pass on Readme
2021-11-03 Updates function board symbol, fixes text that was not vector
2021-11-11 Updates the design to use the Micromod-function device in the official SFE Eagle Libs

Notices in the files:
parts and their libraries:
SparkFun-Aesthetics: Licensing: Creative Commons ShareAlike 4.0 International - https://creativecommons.org/licenses/by-sa/4.0
SparkFun-Aesthetics: Released under the Creative Commons Attribution Share-Alike 4.0 License
SparkFun-Aesthetics: https://creativecommons.org/licenses/by-sa/4.0
